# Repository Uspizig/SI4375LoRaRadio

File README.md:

# SensePuck_Radio: The Triple Tuner Platform for Meshtastic, LoRa, FM & AM

## Features:

1. **2xAudioAmplifier MAX98357**: Listen to your favourite Tunes with an Audio Amplifier

2. **SI4735 with Digital and Analog Audio**: Listen to AM/FM Radio

3. **SI4732 with Analog Audio**: Listen to AM/FM Radio

4.  **Heltec Lora HT-CT62 **: For Recieving and Transmitting LoRa, Meshtastic, TheThingsNetwork, Meshcore or decode your Bresser Weather Station

5.  SI5351 VCO Generator, 3 RF Outputs: 2.5 kHz to 160MHz 

6. **I2C Connector for Sensor**: Connect your favourite I2C Sensor board with the embedded 2.54mm connector

7. **Wireless Control**: Untehther your development process with the wireless capabilities. With WiFi and BLE, this tool allows remote control and data logging. Users can adjust settings and monitor data from a distance, offering a more flexible development experience.

8. **USB-C Connector**: for Debuggung and Power Supply

9. **LSM6 Gyro+ACC**: Check Movements, Steps Pedometer

10. TC4057 Battery Charger (Optional)

11. VEML 7700 Light Sensor (Optional)

12. GPS Sensor (Optional)

13. MLX90640/MLX90614 Thermal Sensor (Optional)

14. **Open Source & Programmable**: As an open-source device, the Device offers unmatched versatility. It is fully programmable, allowing you to tailor its functionality to your specific applications. This customization extends to software and hardware, opening up endless possibilities for creative and efficient project development.

15. **Compact Design**: Designed for convenience, the LoRaCam Board compact and sleek form factor allows for seamless integration into existing setups. Its compatibility with USB PD power sources and inline integration capability minimizes the need for additional equipment or extensive redesign, making it a versatile and user-friendly addition to any development environment.

16. **Display+Touchscreeen**: Monitor live the current status on an 1.8" or 1.28" LCD Touch Display

17. **RTC**: RealTimeClock RV3032 Temp Compensated for RealTime Clock

18. Extension Modules - Compatible to Seeed Sensors and Displays

19. **RGB LED**: Status LED WS2812-4020

20.  BME680: Measure Temperature, Humidity, Air Pressure, TVOC, eCO² (might update to BME688 or BME690 soon)
    
## Specifications

Needed Libaries:

https://github.com/schreibfaul1/ESP32-audioI2S
https://github.com/pololu/lis3mdl-arduino
https://github.com/pololu/lsm6-arduino
https://github.com/Seeed-Projects/SeeedStudio_TFT_eSPI
https://github.com/Seeed-Projects/SeeedStudio_lvgl
https://github.com/Seeed-Studio/Seeed_Arduino_RoundDisplay

### Key Features:

### Future Developments:

AI Detection of objects, radio Signal and determine if the device shall sent the data via LoRa 

## Testing for Performance

At the heart of SensePuck's design is a commitment to reliability and performance. To ensure that SensePuck stands up to real-world demands, we subjected it to testing under use conditions.

## License

MIT License

Copyright (c) 2025 blue2monster

Permission is hereby granted, free of charge, to any person obtaining a copy
of this software and associated documentation files (the "Software"), to deal
in the Software without restriction, including without limitation the rights
to use, copy, modify, merge, publish, distribute, sublicense, and/or sell
copies of the Software, and to permit persons to whom the Software is
furnished to do so, subject to the following conditions:

The above copyright notice and this permission notice shall be included in all
copies or substantial portions of the Software.

THE SOFTWARE IS PROVIDED "AS IS", WITHOUT WARRANTY OF ANY KIND, EXPRESS OR
IMPLIED, INCLUDING BUT NOT LIMITED TO THE WARRANTIES OF MERCHANTABILITY,
FITNESS FOR A PARTICULAR PURPOSE AND NONINFRINGEMENT. IN NO EVENT SHALL THE
AUTHORS OR COPYRIGHT HOLDERS BE LIABLE FOR ANY CLAIM, DAMAGES OR OTHER
LIABILITY, WHETHER IN AN ACTION OF CONTRACT, TORT OR OTHERWISE, ARISING FROM,
OUT OF OR IN CONNECTION WITH THE SOFTWARE OR THE USE OR OTHER DEALINGS IN THE
SOFTWARE.

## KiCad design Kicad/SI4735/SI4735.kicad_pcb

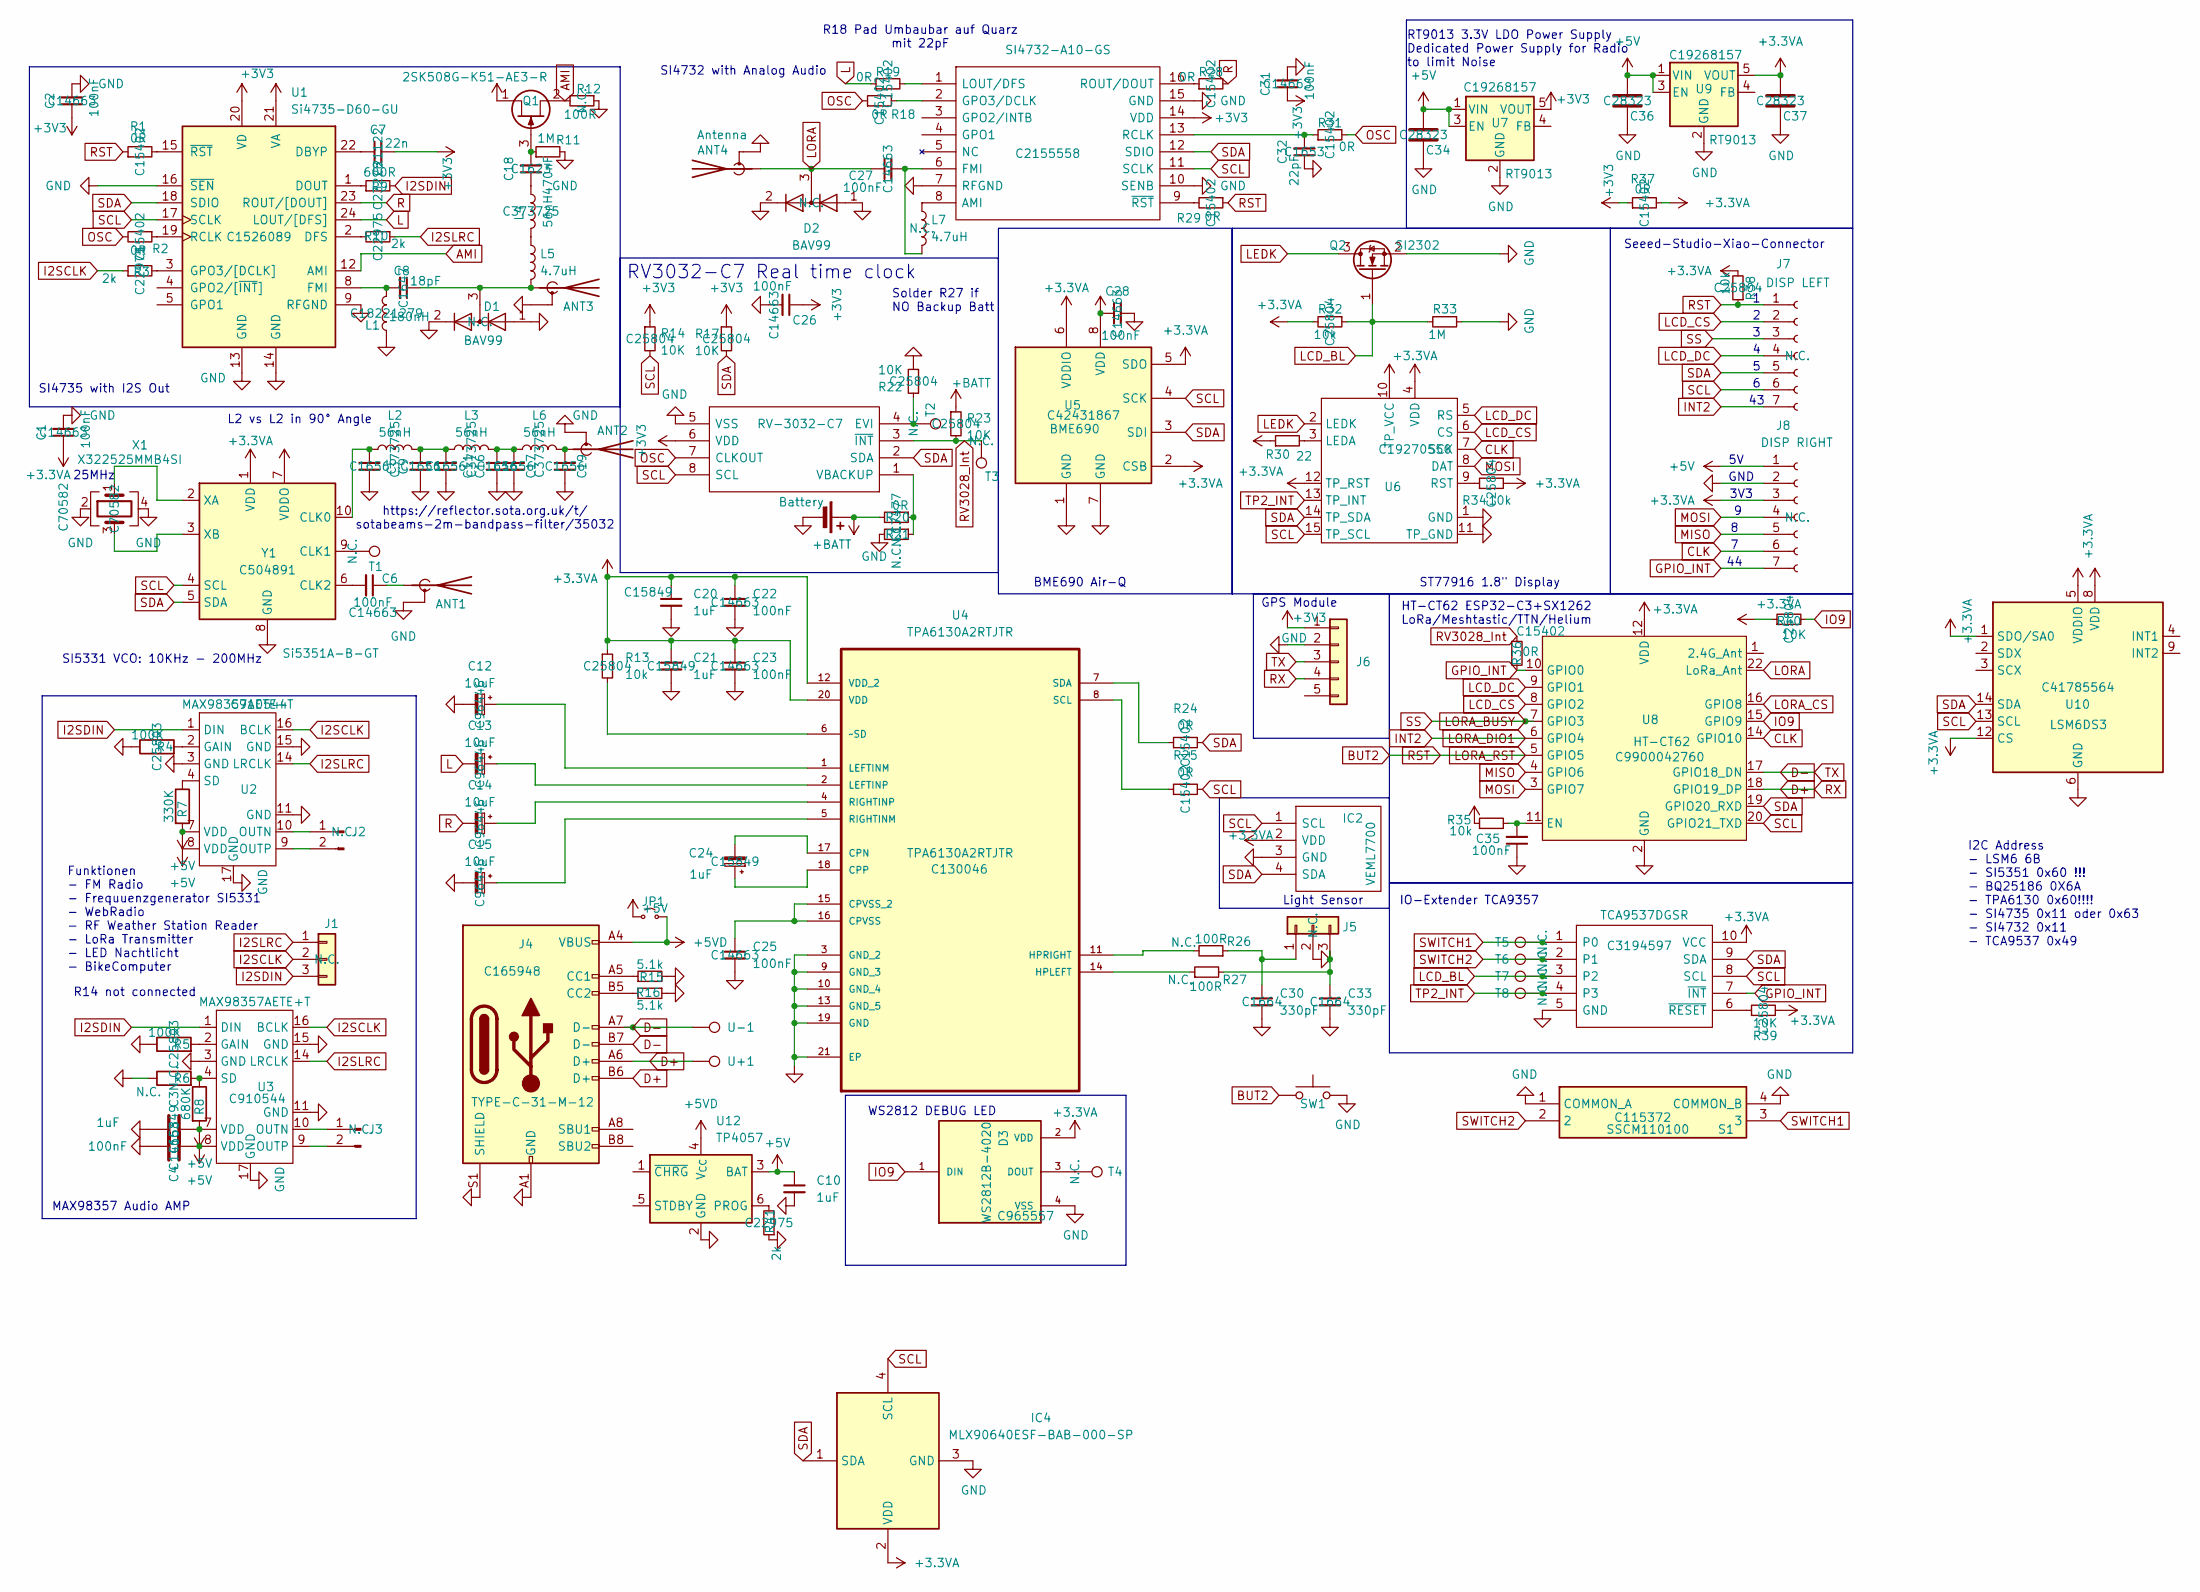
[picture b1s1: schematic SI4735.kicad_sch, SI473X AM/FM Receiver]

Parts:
ANT1, ANT2, ANT3: Antenna_Shield; SMA_Samtec_SMA-J-P-H-ST-EM1_EdgeMount
ANT4: Antenna; SMA_Samtec_SMA-J-P-H-ST-EM1_EdgeMount
BT1: Battery; MYOUNG MY-927-01
C1, C2, C4, C6, C22, C23, C25, C26, C27, C28, C31: 100nF; C_0603_1608Metric; LCSC Part Name C14663
C3, C10, C20, C21, C24: 1uF; C_0603_1608Metric; LCSC Part Name C15849
C5, C9, C11, C16, C17, C19: 27pF; C_0603_1608Metric; LCSC Part Name C1656
C7: 22n; C_0603_1608Metric; LCSC Part Name C21122
C8: 18pF; C_0603_1608Metric; LCSC Part Name C1647
C12, C13, C14, C15: 10uF; C_0603_1608Metric_Pad1.08x0.95mm_HandSolder; LCSC Part Name C96446
C18: 470nF; C_0603_1608Metric; LCSC Part Name C1623
C30, C33: 330pF; C_0603_1608Metric; LCSC Part Name C1664
C32: 22pF; C_0603_1608Metric; LCSC Part Name C1653
C34, C36, C37: 1uF; C_0805_2012Metric_Pad1.18x1.45mm_HandSolder; LCSC Part Name C28323
C35: 100nF; C_0805_2012Metric_Pad1.18x1.45mm_HandSolder
D1, D2: BAV99; SOT-23W; LCSC Part Name N.C.
D3: WS2812B-4020; LED_WS2812B-4020; PARTREV V1.2; LCSC Part Name C965557
IC1: SI4732-A10-GS; SOIC127P600X175-16N; Mouser Part Number 634-SI4732-A10-GS
IC2: VEML7700; Mouser Part Number 78-VEML7700-TR
IC3: TCA9537DGSR; SOP50P490X110-10N; Mouser Part Number 595-TCA9537DGSR
IC4: MLX90640ESF-BAB-000-SP; MLX90640ESFBAB000SP; Mouser Part Number 482-MLX90640ESFBABSP
J1: Conn_01x03; PinHeader_1x03_P2.54mm_Vertical; LCSC Part Name N.C.
J2, J3: Conn_01x02_Pin; PinHeader_1x02_P2.00mm_Vertical; LCSC Part Name N.C.
J4: TYPE-C-31-M-12; USB-C_SMD-TYPE-C-31-M-12; LCSC Part Name C165948
J5: Headphones; PinHeader_1x03_P2.54mm_Vertical_SMD_Pin1Left; LCSC Part Name N.C.
J6: Conn_01x05; PinHeader_1x05_P2.54mm_Vertical_SMD_Pin1Right; LCSC Part Name N.C.
J7: DISP LEFT; PinHeader_1x07_P2.54mm_Vertical; LCSC Part Name N.C.
J8: DISP RIGHT; PinHeader_1x07_P2.54mm_Vertical; LCSC Part Name N.C.
JP1: Jumper_2_Small_Open; SolderJumper-2_P1.3mm_Open_RoundedPad1.0x1.5mm
L1: 180nH; L_0805_2012Metric_Pad1.15x1.40mm_HandSolder; LCSC Part Name C18221279
L2, L3, L4, L6: 56nH; L_0805_2012Metric_Pad1.15x1.40mm_HandSolder; LCSC Part Name C373725
L5: 4.7uH; L_0603_1608Metric_Pad1.05x0.95mm_HandSolder
L7: 4.7uH; L_0603_1608Metric_Pad1.05x0.95mm_HandSolder; LCSC Part Name N.C.
Q1: 2SK508G-K51-AE3-R; SOT-23
Q2: SI2302; SOT-23
R1, R2, R18, R19, R24, R25, R28, R29, R31, R36, R37: 0R; R_0603_1608Metric; LCSC Part Name C15402
R3, R10, R41: 2k; R_0603_1608Metric; LCSC Part Name C22975
R4, R5: 100K; R_0603_1608Metric; LCSC Part Name C25803
R6: N.C.; R_0603_1608Metric_Pad0.98x0.95mm_HandSolder; LCSC Part Name N.C.
R7: 330K; R_0603_1608Metric_Pad0.98x0.95mm_HandSolder
R8: 680K; R_0603_1608Metric_Pad0.98x0.95mm_HandSolder
R9: 600R; R_0603_1608Metric; LCSC Part Name C23228
R11, R33: 1M; R_0603_1608Metric
R12, R26, R27: 100R; R_0603_1608Metric; LCSC Part Name N.C.
R13, R32, R34, R38: 10k; R_0603_1608Metric; LCSC Part Name C25804
R14, R17, R22, R23: 10K; R_0603_1608Metric; LCSC C17414
R15: 5.1k; R_0603_1608Metric
R16: 5.1k; C_0805_2012Metric_Pad1.18x1.45mm_HandSolder
R20: 0R; R_0603_1608Metric_Pad0.98x0.95mm_HandSolder; LCSC C17477
R21: N.C.; R_0603_1608Metric_Pad0.98x0.95mm_HandSolder; LCSC C17414
R30: 22; R_0603_1608Metric
R35: 10k; R_0805_2012Metric_Pad1.20x1.40mm_HandSolder
R39, R40: 10K; R_0603_1608Metric; LCSC Part Name C25804
S1: SSCM110100; Mouser Part Number 688-SSCM110100
SW1: SW_Push; SW-SMD_4P-CORR-L5.2-W5.2-P3.70-LS6.4
T1, T2, T3, T4, T5, T6, T7, T8: TestPoint; TestPoint_Pad_D1.0mm; LCSC Part Name N.C.
U1: Si4735-D60-GU; SSOP-24_3.9x8.7mm_P0.635mm; LCSC Part Name C1526089
U2, U3: MAX98357AETE+T; TQFN-16_L3.0-W3.0-P0.50-BL-EP1.5; LCSC Part Name C910544
U4: TPA6130A2RTJTR; QFN-20-1EP_4x4mm_P0.5mm_EP2.7x2.7mm; MPN TPA6130A2RTJTR; LCSC Part Name C130046
U5: BME690; Bosch_LGA-8_3x3mm_P0.8mm_ClockwisePinNumbering; LCSC Part Name C42431867
U6: GC9A01_Touch_IPS_display_reversed_16pin; LCSC Part Name C19270550
U7, U9: RT9013; SOT-23-5; LCSC Part Name C19268157
U8: HT-CT62; Heltec_HT-CT62; LCSC Part Name C9900042760
U10: LSM6DS3; LGA-14_3x2.5mm_P0.5mm_LayoutBorder3x4y; LCSC Part Name C41785564
U12: TP4057; TSOT-23-6; LCSC Part Name C12044
U+1: U+; TestPoint_Pad_D1.0mm; LCSC Part Name N.C.
U-1: U-; TestPoint_Pad_D1.0mm; LCSC Part Name N.C.
X1: X322525MMB4SI; Crystal_SMD_3225-4Pin_3.2x2.5mm; LCSC Part Name C70582
Y1: Si5351A-B-GT; MSOP-10_3x3mm_P0.5mm; LCSC Part Name C504891
Y2: RV-3032-C7; RV3032C7; Mouser Part Number 428-203853-MG01

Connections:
+3.3VA: C1.1, C20.1, C21.1, C22.1, C23.1, C28.1, C37.2, D3.2 (VDD), IC2.2 (VDD), IC3.10 (VCC), IC4.2 (VDD), J8.3, R13.1, R30.1, R32.2, R34.2, R37.2, R38.2, R39.2, R40.1, U4.12 (VDD_2), U4.20 (VDD), U5.2 (CSB), U5.5 (SDO), U5.6 (VDDIO), U5.8 (VDD), U6.4 (VDD), U6.10 (TP_VCC), U6.12 (TP_RST), U8.12 (VDD), U9.5 (VOUT), U10.1 (SDO/SA0), U10.5 (VDDIO), U10.8 (VDD), U10.12 (CS), Y1.1 (VDD), Y1.7 (VDDO)
+3V3: C2.1, C7.2, C26.1, C31.1, IC1.14 (VDD), J6.1, Q1.1 (D), R14.1, R17.1, R35.1, R37.1, U1.20 (VD), U1.21 (VA), U7.5 (VOUT), Y2.6 (VDD)
+5V: C3.1, C4.1, C10.1, C34.2, C36.2, J8.1, JP1.2 (B), R7.2, R8.2, U2.7 (VDD), U2.8 (VDD), U3.7 (VDD), U3.8 (VDD), U7.1 (VIN), U7.3 (EN), U9.1 (VIN), U9.3 (EN), U12.3 (BAT)
+5VD: J4.A4 (VBUS), J4.A9 (VBUS), J4.B4 (VBUS), J4.B9 (VBUS), JP1.1 (A), U12.4 (V_{CC})
+BATT: BT1.1 (+), R20.2, R23.1
AMI: Q1.2 (S), R12.2, U1.12 (AMI)
BUT2: J7.1, R1.1, R29.1, R38.1, SW1.1, U8.5 (GPIO5)
CLK: J8.6, U6.7 (SCK), U8.14 (GPIO10)
D+: J4.A6 (D+), J4.B6 (D+), J6.4, U8.18 (GPIO19_DP), U+1.1
D-: J4.A7 (D-), J4.B7 (D-), J6.3, U8.17 (GPIO18_DN), U-1.1
GND: ANT1.2 (Shield), ANT2.2 (Shield), ANT3.2 (Shield), ANT4.2 (Shield), BT1.2 (-), C1.2, C2.2, C3.2, C4.2, C5.2, C9.2, C10.2, C11.2, C12.2, C15.2, C16.2, C17.2, C19.2, C20.2, C21.2, C22.2, C23.2, C25.2, C26.2, C28.2, C30.2, C31.2, C32.1, C33.2, C34.1, C35.1, C36.1, C37.1, D1.1 (K), D1.2 (A), D2.1 (K), D2.2 (A), D3.4 (VSS), IC1.7 (RFGND), IC1.10 (SENB), IC1.15 (GND), IC2.3 (GND), IC3.5 (GND), IC4.3 (GND), J4.A1 (GND), J4.A12 (GND), J4.B1 (GND), J4.B12 (GND), J4.S1 (SHIELD), J5.2, J6.2, J8.2, L1.1, Q2.2 (S), R4.1, R5.1, R6.1, R11.2, R12.1, R15.2, R16.1, R21.2, R22.2, R33.1, R41.1, S1.1 (COMMON_A), S1.4 (COMMON_B), SW1.2, U1.9 (RFGND), U1.13 (GND), U1.14 (GND), U1.16 (~SEN), U2.3 (GND), U2.11 (GND), U2.15 (GND), U2.17 (GND), U3.3 (GND), U3.11 (GND), U3.15 (GND), U3.17 (GND), U4.3 (GND_2), U4.9 (GND_3), U4.10 (GND_4), U4.13 (GND_5), U4.19 (GND), U4.21 (EP), U5.1 (GND), U5.7 (GND), U6.1 (GND), U6.11 (TP_GND), U7.2 (GND), U8.2 (GND), U8.13 (GND), U8.21 (GND), U9.2 (GND), U10.6 (GND), U10.7 (GND), U12.2 (GND), X1.2, X1.4, Y1.8 (GND), Y2.5 (VSS)
GPIO_INT: IC3.7 (~INT), J8.7, R36.2, U8.10 (GPIO0)
I2SCLK: J1.2, R3.1, U2.16 (BCLK), U3.16 (BCLK)
I2SDIN: J1.3, R9.2, U2.1 (DIN), U3.1 (DIN)
I2SLRC: J1.1, R10.1, U2.14 (LRCLK), U3.14 (LRCLK)
INT2: J7.7, U8.6 (GPIO4)
IO9: D3.1 (DIN), R40.2, U8.15 (GPIO9)
L: C13.2, R19.1, U1.24 (LOUT/[DFS])
LCD_BL: IC3.3 (P2), Q2.1 (G), R32.1, R33.2, T7.1
LCD_CS: J7.2, U6.6 (CS), U8.8 (GPIO2)
LCD_DC: J7.4, U6.5 (RS), U8.9 (GPIO1)
LEDK: Q2.3 (D), U6.2 (LEDK)
LORA: ANT4.1 (A), C27.1, D2.3 (K), U8.22 (LoRa_Ant)
LORA_BUSY: J7.3, U8.7 (GPIO3)
LORA_CS: U8.16 (GPIO8)
MISO: J8.5, U8.4 (GPIO6)
MOSI: J8.4, U6.8 (DAT), U8.3 (GPIO7)
unnamed: ANT1.1 (A), C6.1
unnamed: ANT2.1 (A), C19.1, L6.2
unnamed: ANT3.1 (A), C8.1, D1.3 (K), L5.2
unnamed: C9.1, C11.1, L2.2, L3.1
unnamed: C16.1, C17.1, L3.2, L6.1
unnamed: C18.1, L4.1
unnamed: D3.3 (DOUT), T4.1
unnamed: IC1.8 (AMI), L7.1
unnamed: C27.2, IC1.6 (FMI), L7.2
unnamed: IC1.2 (GPO3/DCLK), R18.2
unnamed: IC1.1 (LOUT/DFS), R19.2
unnamed: C32.2, IC1.13 (RCLK), R31.1
unnamed: IC1.16 (ROUT/DOUT), R28.1
unnamed: IC1.9 (~RST), R29.2
unnamed: IC3.6 (~RESET), R39.1
unnamed: J2.1, U2.10 (OUTN)
unnamed: J2.2, U2.9 (OUTP)
unnamed: J3.1, U3.10 (OUTN)
unnamed: J3.2, U3.9 (OUTP)
unnamed: J4.A5 (CC1), R15.1
unnamed: J4.B5 (CC2), R16.2
unnamed: C30.1, J5.1, R26.1
unnamed: C33.1, J5.3, R27.2
unnamed: L4.2, L5.1
unnamed: C18.2, Q1.3 (G), R11.1
unnamed: C7.1, U1.22 (DBYP)
unnamed: R10.2, U1.2 (DFS)
unnamed: R9.1, U1.1 (DOUT)
unnamed: C8.2, L1.2, U1.8 (FMI)
unnamed: R3.2, U1.3 (GPO3/[DCLK])
unnamed: R2.1, U1.19 (RCLK)
unnamed: R1.2, U1.15 (~RST)
unnamed: R4.2, U2.2 (GAIN)
unnamed: R7.1, U2.4 (SD)
unnamed: R5.2, U3.2 (GAIN)
unnamed: R6.2, R8.1, U3.4 (SD)
unnamed: C24.2, U4.17 (CPN)
unnamed: C24.1, U4.18 (CPP)
unnamed: C25.1, U4.15 (CPVSS_2), U4.16 (CPVSS)
unnamed: R27.1, U4.14 (HPLEFT)
unnamed: R26.2, U4.11 (HPRIGHT)
unnamed: C12.1, U4.1 (LEFTINM)
unnamed: C13.1, U4.2 (LEFTINP)
unnamed: C15.1, U4.5 (RIGHTINM)
unnamed: C14.1, U4.4 (RIGHTINP)
unnamed: R25.1, U4.8 (SCL)
unnamed: R24.1, U4.7 (SDA)
unnamed: R13.2, U4.6 (~SD)
unnamed: R30.2, U6.3 (LEDA)
unnamed: R34.1, U6.9 (RST)
unnamed: C35.2, R35.2, U8.11 (EN)
unnamed: R41.2, U12.6 (PROG)
unnamed: C5.1, L2.1, Y1.10 (CLK0)
unnamed: T1.1, Y1.9 (CLK1)
unnamed: C6.2, Y1.6 (CLK2)
unnamed: X1.1, Y1.2 (XA)
unnamed: X1.3, Y1.3 (XB)
unnamed: R22.1, T2.1, Y2.4 (EVI)
unnamed: R20.1, R21.1, Y2.1 (VBACKUP)
OSC: R2.2, R18.1, R31.2, Y2.7 (CLKOUT)
R: C14.2, R28.2, U1.23 (ROUT/[DOUT])
RV3028_Int: R23.2, R36.1, T3.1, Y2.3 (~INT)
SCL: IC1.11 (SCLK), IC2.1 (SCL), IC3.8 (SCL), IC4.4 (SCL), J7.6, R14.2, R25.2, U1.17 (SCLK), U5.4 (SCK), U6.15 (TP_SCL), U8.20 (GPIO21_TXD), U10.13 (SCL), Y1.4 (SCL), Y2.8 (SCL)
SDA: IC1.12 (SDIO), IC2.4 (SDA), IC3.9 (SDA), IC4.1 (SDA), J7.5, R17.2, R24.2, U1.18 (SDIO), U5.3 (SDI), U6.14 (TP_SDA), U8.19 (GPIO20_RXD), U10.14 (SDA), Y1.5 (SDA), Y2.2 (SDA)
SWITCH1: IC3.1 (P0), S1.3, T5.1
SWITCH2: IC3.2 (P1), S1.2, T6.1
TP2_INT: IC3.4 (P3), T8.1, U6.13 (TP_INT)

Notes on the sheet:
I2C Address - LSM6 6B - SI5351 0x60 !!! - BQ25186 0X6A - TPA6130 0x60!!!! - SI4735 0x11 oder 0x63 - SI4732 0x11 - TCA9537 0x49
RT9013 3.3V LDO Power Supply Dedicated Power Supply for Radio to limit Noise
SI4732 with Analog Audio
Solder R27 if NO Backup Batt
R14 not connected
MAX98357 Audio AMP
3V3
Funktionen - FM Radio - Frequuenzgenerator SI5331 - WebRadio - RF Weather Station Reader - LoRa Transmitter - LED Nachtlicht - BikeComputer
Light Sensor
WS2812 DEBUG LED
Seeed-Studio-Xiao-Connector
IO-Extender TCA9357
RV3032-C7 Real time clock
SI5331 VCO: 10KHz - 200MHz
https://reflector.sota.org.uk/t/ sotabeams-2m-bandpass-filter/35032
BME690 Air-Q
HT-CT62 ESP32-C3+SX1262 LoRa/Meshtastic/TTN/Helium
25MHz
L2 vs L2 in 90° Angle
SI4735 with I2S Out
GND
R18 Pad Umbaubar auf Quarz mit 22pF
ST77916 1.8" Display
GPS Module

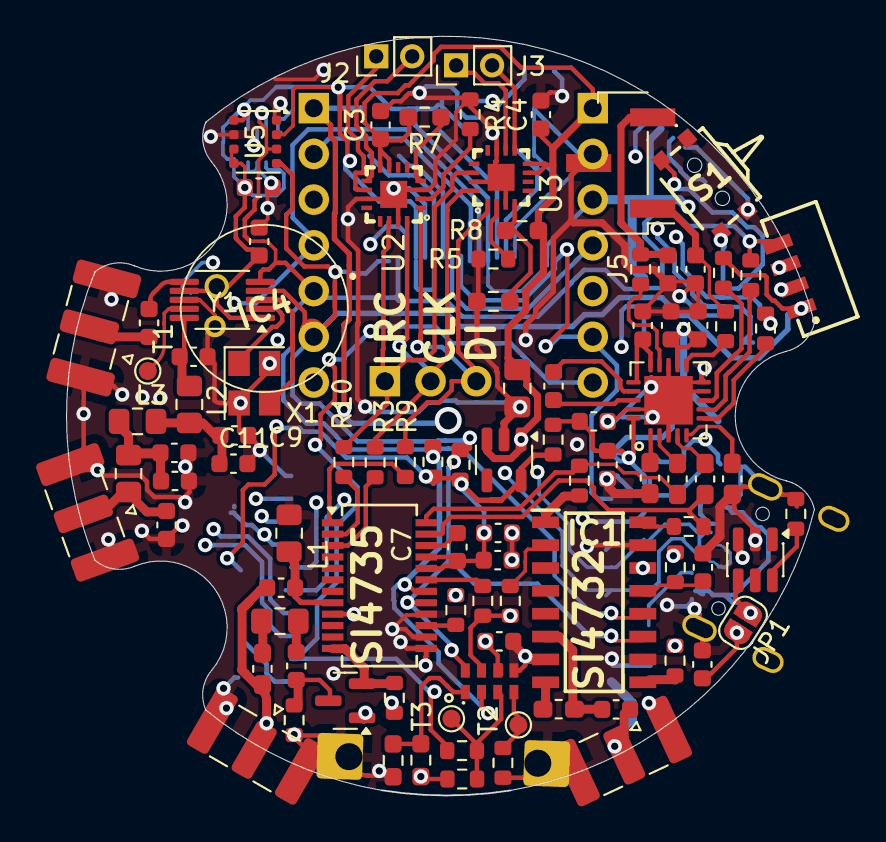
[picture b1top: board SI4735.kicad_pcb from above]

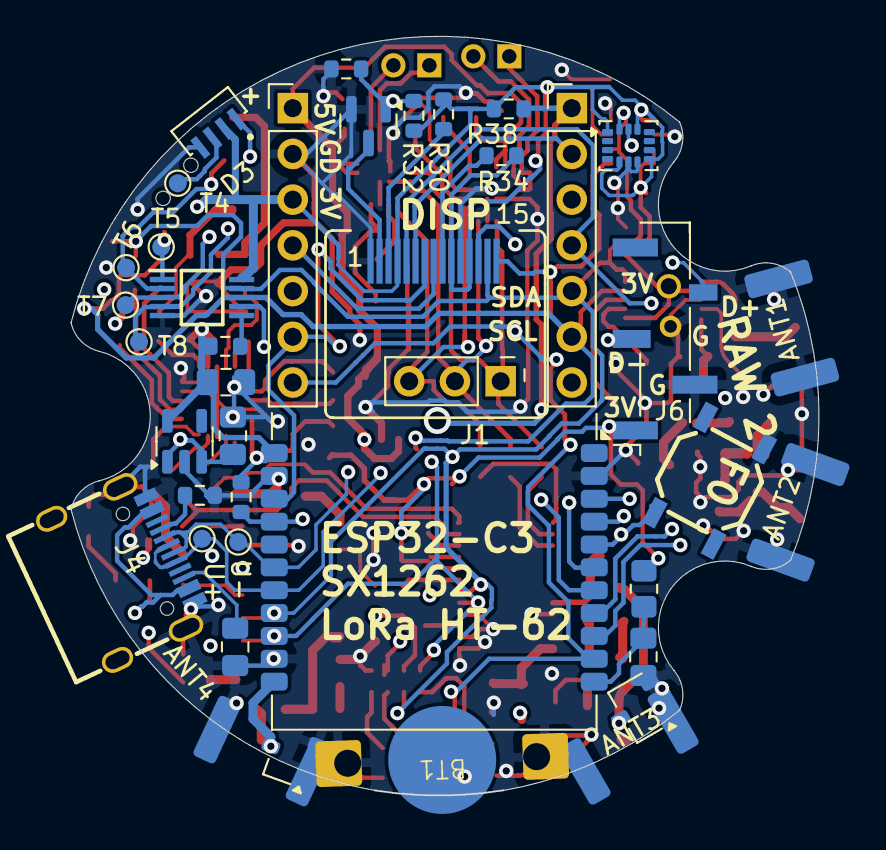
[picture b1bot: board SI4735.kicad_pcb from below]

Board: 4 copper layers, 41.6 x 42.2 mm, 133 parts (36 on the bottom side), 93 nets.

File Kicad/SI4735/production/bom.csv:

Designator,Footprint,Quantity,Value,LCSC Part #
"ANT1, ANT2, ANT3",SMA_Samtec_SMA-J-P-H-ST-EM1_EdgeMount,3,Antenna_Shield,
ANT4,SMA_Samtec_SMA-J-P-H-ST-EM1_EdgeMount,1,Antenna,
BT1,MYOUNG MY-927-01,1,Battery,
"C1, C2, C22, C23, C25, C26, C27, C28, C31, C4, C6",0603,11,100nF,
"C10, C20, C21, C24, C3",0603,5,1uF,
"C11, C16, C17, C19, C5, C9",0603,6,27pF,
"C12, C13, C14, C15",0603,4,10uF,
C18,0603,1,470nF,
"C30, C33",0603,2,330pF,
C32,0603,1,22pF,
"C34, C36, C37",0805,3,1uF,
C35,0805,1,100nF,
C7,0603,1,22n,
C8,0603,1,18pF,
"D1, D2",SOT-23W,2,BAV99,
D3,LED_WS2812B-4020,1,WS2812B-4020,
IC1,SOIC127P600X175-16N,1,SI4732-A10-GS,
IC2,VEML7700,1,VEML7700,
IC3,SOP50P490X110-10N,1,TCA9537DGSR,
IC4,MLX90640ESFBAB000SP,1,MLX90640ESF-BAB-000-SP,
J1,PinHeader_1x03_P2.54mm_Vertical,1,Conn_01x03,
"J2, J3",PinHeader_1x02_P2.00mm_Vertical,2,Conn_01x02_Pin,
J4,USB-C_SMD-TYPE-C-31-M-12,1,TYPE-C-31-M-12,
J5,PinHeader_1x03_P2.54mm_Vertical_SMD_Pin1Left,1,Headphones,
J6,PinHeader_1x05_P2.54mm_Vertical_SMD_Pin1Right,1,Conn_01x05,
J7,PinHeader_1x07_P2.54mm_Vertical,1,DISP LEFT,
J8,PinHeader_1x07_P2.54mm_Vertical,1,DISP RIGHT,
JP1,SolderJumper-2_P1.3mm_Open_RoundedPad1.0x1.5mm,1,Jumper_2_Small_Open,
L1,0805,1,180nH,
"L2, L3, L4, L6",0805,4,56nH,
"L5, L7",0603,2,4.7uH,
Q1,SOT-23,1,2SK508G-K51-AE3-R,
Q2,SOT-23,1,SI2302,
"R1, R18, R19, R2, R24, R25, R28, R29, R31, R36, R37",0603,11,0R,
"R10, R3, R41",0603,3,2k,
"R11, R33",0603,2,1M,
"R12, R26, R27",0603,3,100R,
"R13, R32, R34, R38, R39, R40",0603,6,10k,
"R14, R17, R22, R23",0603,4,10K,C17414
R15,0603,1,5.1k,
R16,0805,1,5.1k,
R20,0603,1,0R,C17477
R21,0603,1,N.C.,C17414
R30,0603,1,22,
R35,0805,1,10k,
"R4, R5",0603,2,100K,
R6,0603,1,N.C.,
R7,0603,1,330K,
R8,0603,1,680K,
R9,0603,1,600R,
S1,SSCM110100,1,SSCM110100,
SW1,SW-SMD_4P-CORR-L5.2-W5.2-P3.70-LS6.4,1,SW_Push,
"T1, T2, T3, T4, T5, T6, T7, T8",TestPoint_Pad_D1.0mm,8,TestPoint,
U+1,TestPoint_Pad_D1.0mm,1,U+,
U-1,TestPoint_Pad_D1.0mm,1,U-,
U1,SSOP-24_3.9x8.7mm_P0.635mm,1,Si4735-D60-GU,
U10,LGA-14_3x2.5mm_P0.5mm_LayoutBorder3x4y,1,LSM6DS3,
U12,TSOT-23-6,1,TP4057,
"U2, U3",TQFN-16_L3.0-W3.0-P0.50-BL-EP1.5,2,MAX98357AETE+T,
U4,QFN-20-1EP_4x4mm_P0.5mm_EP2.7x2.7mm,1,TPA6130A2RTJTR,  TPA6130A2RTJTR
U5,Bosch_LGA-8_3x3mm_P0.8mm_ClockwisePinNumbering,1,BME690,
U6,GC9A01_Touch_IPS_display_reversed_16pin,1,~,
"U7, U9",SOT-23-5,2,RT9013,
U8,Heltec_HT-CT62,1,HT-CT62,
X1,Crystal_SMD_3225-4Pin_3.2x2.5mm,1,X322525MMB4SI,
Y1,MSOP-10_3x3mm_P0.5mm,1,Si5351A-B-GT,
Y2,RV3032C7,1,RV-3032-C7,

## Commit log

2025-12-16 Initial Upload
2025-12-16 Update README.md
    Added Schematic IMG
2025-12-19 Add files via upload
    - Rotation of SI4732 Radio
    - Added Battery Charging IC TP4057
    - Added Light Sensor VEML7700
2025-12-21 Add files via upload
    - Added MLX90640 Thermal Camera
    - Refinement of inner Layers to enhance EMC
2025-12-22 Updated to last Design with rotated SI4732
    - Added Battery charger
    - Added MLX90640 Thermal CAM
    - Added rotation of SI4732 Chip
    - Renamed Chips
2025-12-22 Add files via upload
    Added new Schematic File
